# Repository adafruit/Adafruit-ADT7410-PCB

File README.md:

## Adafruit ADT7410 High Accuracy I2C Temperature Sensor Breakout Board PCB

<a href="http://www.adafruit.com/products/4089"><br/>
Click here to purchase one from the Adafruit shop</a>

PCB files for the Adafruit ADT7410 High Accuracy I2C Temperature Sensor Breakout Board. Format is EagleCAD schematic and board layout
* https://www.adafruit.com/product/4089

### Description

Analog Devices, known for their reliable and well-documented sensor chips - has a high precision and high resolution temperature sensor on the market, and we've got a breakout to make it easy to use! The Analog Devices ADT7410 gets straight to the point - it's an I2C temperature sensor, with 16-bit 0.0078°C temperature resolution and 0.5°C temperature tolerance. Wire it up to your microcontroller or single-board computer to get reliable temperature readings with ease

The ADT7410 has 2 address pins, so you can have up to 4 sensors on one I2C bus. There's also interrupt and critical-temperature alert pins. The sensor is good from 2.7V to 5.5V power and logic, for easy integration.

We've got both [Arduino (C/C++)](https://learn.adafruit.com/adt7410-breakout/arduino) and [CircuitPython (Python 3)](https://learn.adafruit.com/adt7410-breakout/python-and-circuitpython) libraries available so you can [use it with any microcontroller like Arduino](https://learn.adafruit.com/adt7410-breakout/arduino), ESP8266, Metro, etc or with [Raspberry Pi or other Linux computers thanks to Blinka (our CircuitPython library support helper).](https://learn.adafruit.com/adt7410-breakout/python-and-circuitpython)

To get you going fast, we spun up a custom made PCB with the ADT7410 and some supporting circuitry such as pullup resistors and capacitors, in the STEMMA QT form factor, making them easy to interface with. The STEMMA QT connectors on either side are compatible with the SparkFun Qwiic I2C connectors. This allows you to make solderless connections between your development board and the ADT7410 or to chain them with a wide range of other sensors and accessories using a compatible cable. QT Cable is not included, but we have a variety in the shop.

Each order comes with a fully tested and assembled breakout and some header for soldering to a PCB or breadboard. You'll be up and running in under 5 minutes!

[Thanks to Digi-Key](https://www.digikey.com/) and [Analog Devices](https://www.analog.com/en/index.html) for sponsoring the development of this breakout board - we've made the PCB "[Digi-Key red](https://www.digikey.com/)" in their honor!

### License

Adafruit invests time and resources providing this open source design, please support Adafruit and open-source hardware by purchasing products from [Adafruit](https://www.adafruit.com)!

Designed by Limor Fried/Ladyada for Adafruit Industries.

Creative Commons Attribution/Share-Alike, all text above must be included in any redistribution. See license.txt for additional details.

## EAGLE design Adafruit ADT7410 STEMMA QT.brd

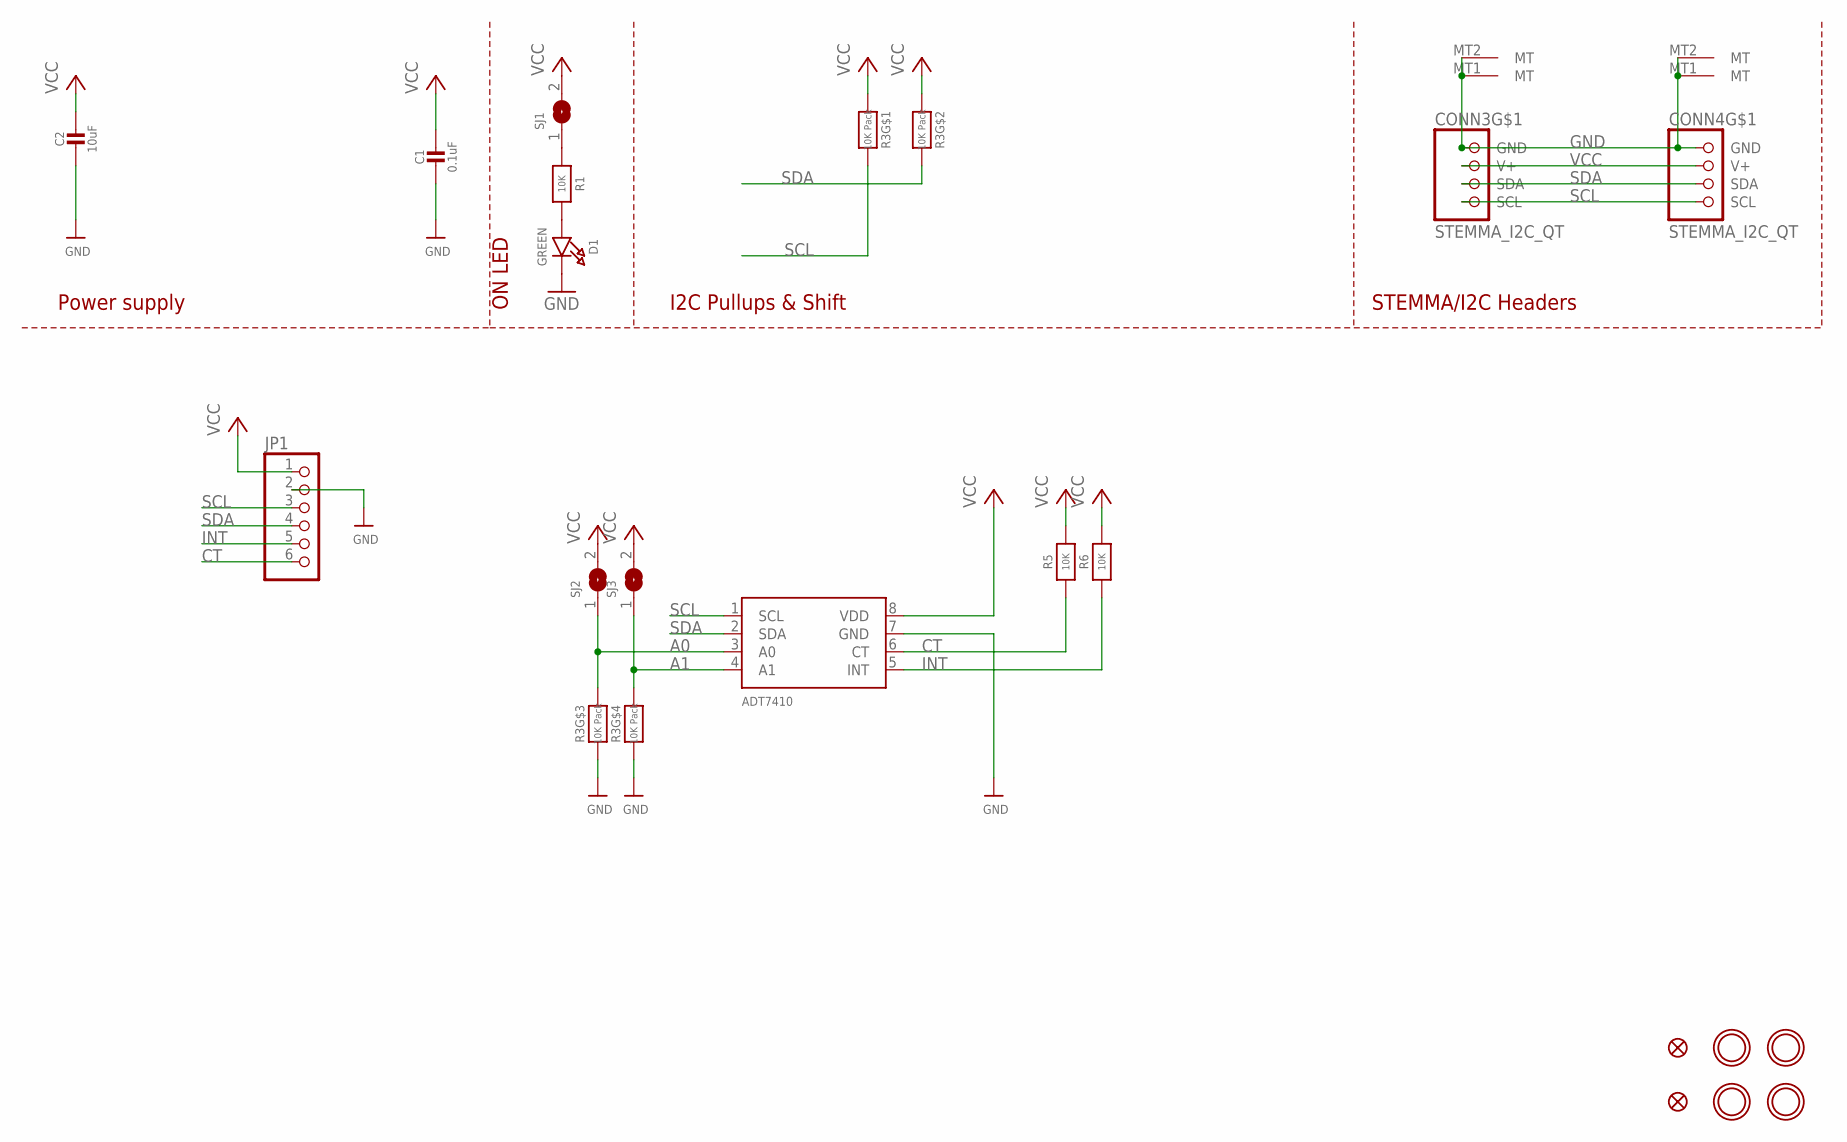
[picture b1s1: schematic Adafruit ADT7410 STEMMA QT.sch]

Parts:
C1: 0.1uF; 0603-NO
C2: 10uF; 0805-NO
CONN3, CONN4: STEMMA_I2C_QT; JST_SH4
D1: GREEN; CHIPLED_0603_NOOUTLINE
FID3, FID4: FIDUCIAL_1MM
JP1: HEADER-1X670MIL; 1X06_ROUND_70
R1, R5, R6: 10K; 0603-NO
R3: 10K Pack; RESPACK_4X0603
SJ1: SOLDERJUMPERCLOSED; SOLDERJUMPER_CLOSEDWIRE
SJ2, SJ3: SOLDERJUMPER; SOLDERJUMPER_ARROW_NOPASTE
U1: ADT7410; SOIC8_150MIL
U$1, U$17, U$19, U$21: MOUNTINGHOLE2.5; MOUNTINGHOLE_2.5_PLATED

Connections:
A0: R3.6 (2), SJ2.1, U1.3 (A0)
A1: R3.5 (2), SJ3.1, U1.4 (A1)
CT: JP1.6, R5.1, U1.6 (CT)
GND: C1.2, C2.2, CONN3.1 (GND), CONN3.MT1 (MT), CONN3.MT2 (MT), CONN4.1 (GND), CONN4.MT1 (MT), CONN4.MT2 (MT), D1.C, JP1.2, R3.3 (1), R3.4 (1), U1.7 (GND)
INT: JP1.5, R6.1, U1.5 (INT)
unnamed: D1.A, R1.2
unnamed: R1.1, SJ1.1
SCL: CONN3.4 (SCL), CONN4.4 (SCL), JP1.3, R3.8 (2), U1.1 (SCL)
SDA: CONN3.3 (SDA), CONN4.3 (SDA), JP1.4, R3.7 (2), U1.2 (SDA)
VCC: C1.1, C2.1, CONN3.2 (V+), CONN4.2 (V+), JP1.1, R3.1, R3.2 (1), R5.2, R6.2, SJ1.2, SJ2.2, SJ3.2, U1.8 (VDD)

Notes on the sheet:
I2C Pullups & Shift
STEMMA/I2C Headers
ON LED
Power supply

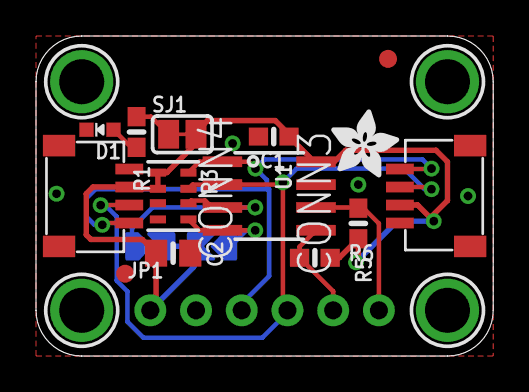
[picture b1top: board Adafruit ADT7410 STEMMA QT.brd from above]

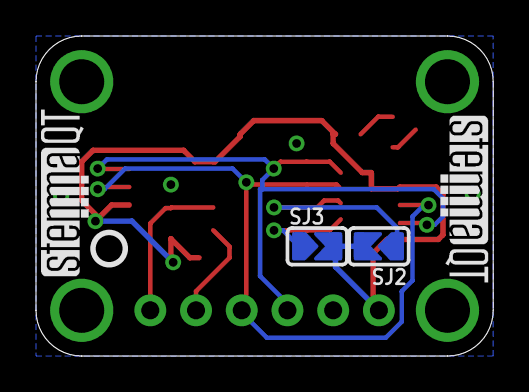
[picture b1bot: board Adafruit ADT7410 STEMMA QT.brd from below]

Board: 2 copper layers, 25.4 x 17.8 mm, 40 parts (12 on the bottom side), 10 nets.

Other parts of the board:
PLABEL0: PLABEL0
PLABEL1: PLABEL1
PLABEL2: PLABEL2
PLABEL3: PLABEL3
PLABEL4: PLABEL4
PLABEL5: PLABEL5
PLABEL6: PLABEL6
PLABEL7: PLABEL7
PLABEL8: PLABEL8
PLABEL9: PLABEL9
PLABEL10: PLABEL10
PLABEL11: PLABEL11
PLABEL12: PLABEL12
PLABEL13: PLABEL13
PLABEL14: PLABEL14
PLABEL15: PLABEL15
U$22: ADAFRUIT_3.5MM
U$25: PCBFEAT-REV-040
U$30, U$31: STEMMAQT

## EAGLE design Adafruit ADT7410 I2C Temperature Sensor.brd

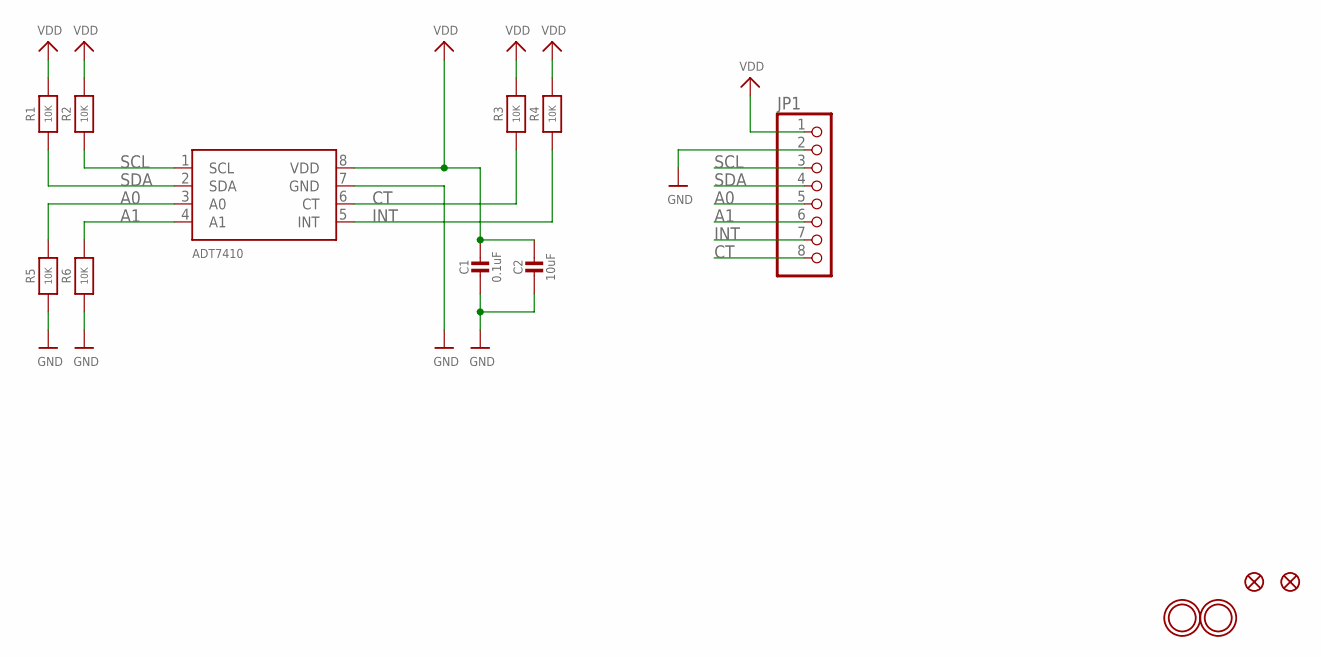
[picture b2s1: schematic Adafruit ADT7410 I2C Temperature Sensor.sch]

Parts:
C1: 0.1uF; 0603-NO
C2: 10uF; 0805-NO
FID1, FID2: FIDUCIAL_1MM
JP1: HEADER-1X870MIL; 1X08_ROUND_70
R1, R2, R3, R4, R5, R6: 10K; 0603-NO
U1: ADT7410; SOIC8_150MIL
U$3, U$4: MOUNTINGHOLE2.0; MOUNTINGHOLE_2.0_PLATED

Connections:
A0: JP1.5, R5.2, U1.3 (A0)
A1: JP1.6, R6.2, U1.4 (A1)
CT: JP1.8, R3.1, U1.6 (CT)
GND: C1.2, C2.2, JP1.2, R5.1, R6.1, U1.7 (GND)
INT: JP1.7, R4.1, U1.5 (INT)
SCL: JP1.3, R2.1, U1.1 (SCL)
SDA: JP1.4, R1.1, U1.2 (SDA)
VDD: C1.1, C2.1, JP1.1, R1.2, R2.2, R3.2, R4.2, U1.8 (VDD)

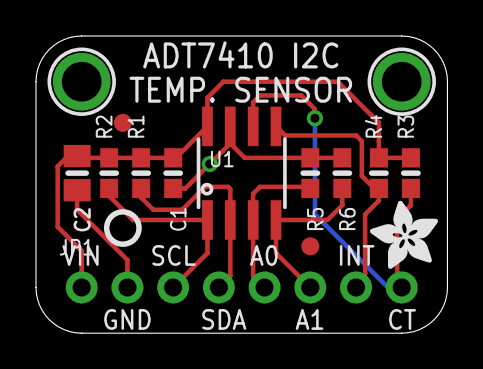
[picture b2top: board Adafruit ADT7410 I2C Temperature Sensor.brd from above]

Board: 2 copper layers, 22.9 x 16.5 mm, 16 parts (0 on the bottom side), 8 nets.

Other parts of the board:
U$1: PCBFEAT-REV-040
U$16: ADAFRUIT_3.5MM

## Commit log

2019-02-06 Adding brd and sch files.
2019-02-06 Clean gh-pages branch
2019-07-17 updated to use cookiecutter for pcb repos
2023-04-17 adding stemma version

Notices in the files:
parts and their libraries:
microbuilder: This work is placed in the public domain, and may be freely used for commercial and non-commercial work with the following conditions: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
